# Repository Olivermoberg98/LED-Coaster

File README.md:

# LED Coaster

A battery-powered drink coaster with two rings of addressable RGB LEDs, controlled
from an Android phone over Bluetooth LE. The repository holds the whole project:
ESP32-C3 firmware, the Android app, the KiCad board and the 3D-printed enclosure.

- **Coaster:** 90 mm round board, ESP32-C3, 10 LEDs on the front and 20 around
  the back, a 1S Li-Po charged over USB-C, and a slide switch.
- **App:** finds coasters, sets each ring's pattern (fixed, pulse, chaser,
  rainbow) and colour, shows battery and charge state, and runs party games
  across several coasters at once.
- **Firmware:** reports battery voltage, percentage and charger state to the
  app, caps LED current as the cell runs down, and shuts off before the cell is
  empty.

## How it fits together

```
 Android app  ── BLE write:  Package 1 (rings on/off), Package 2 (pattern + colour) ──▶  coaster
              ◀── BLE notify: Package 3 (battery voltage, %, charger state) ──────────
```

The coaster is a GATT server with one command characteristic and one status
characteristic. Every packet carries a one-byte checksum, and the firmware drops
any packet that fails to parse. Byte layouts, UUIDs and the rules both sides
must keep in step are in [CLAUDE.md](CLAUDE.md#the-ble-contract-the-thing-that-spans-both-halves).

| Folder | Contents |
|---|---|
| [`Software/LED_coaster/`](Software/LED_coaster/) | Firmware: PlatformIO, Arduino, FastLED, NimBLE |
| [`Software/App/Coaster_app/`](Software/App/Coaster_app/) | Android app: Kotlin, Jetpack Compose, Nordic BLE library |
| [`Hardware/PCB/`](Hardware/PCB/) | KiCad project, JLCPCB production files, board checker; see its [README](Hardware/PCB/README.md) |
| [`Hardware/3d_printing/`](Hardware/3d_printing/) | Enclosure: STEP source plus print-ready STL/3MF for the top shell and bottom piece |

[CLAUDE.md](CLAUDE.md) and [the app's CLAUDE.md](Software/App/Coaster_app/CLAUDE.md)
are the detailed developer guides: architecture, protocol, power budget,
bring-up measurements and the battery discharge curve. They are written as
instructions for the Claude Code assistant but read fine as engineering notes.

## Building

### Firmware

Needs [PlatformIO](https://platformio.org/install/cli). Flashing and the serial
log both go over the coaster's USB-C port; no adapter is needed.

```sh
cd Software/LED_coaster
pio run                  # build
pio run -t upload        # flash
pio device monitor       # serial log
```

Every coaster needs its own ID. Set `coasterID` in
[`src/main.cpp`](Software/LED_coaster/src/main.cpp) before flashing each board.
It becomes the Bluetooth name `Coaster-<id>`. Two extra environments exist for
testing: `battery-fake` cycles through every battery and charger state for app
development, and `rundown` logs a full discharge to flash for fitting the
battery curve.

### Android app

Needs Android Studio, or the Android SDK with JDK 17. The app runs on
Android 12 (API 31) and newer, and needs a real phone, because the emulator has
no Bluetooth.

```sh
cd Software/App/Coaster_app
./gradlew assembleDebug  # build (gradlew.bat on Windows)
./gradlew installDebug   # install on a connected phone
./gradlew test lint      # unit tests and lint
```

### PCB

Open `Hardware/PCB/LED_Coaster.kicad_pro` in KiCad 10. The board was assembled
by JLCPCB from the files in `production/`, with the back side soldered by
hand. [`Hardware/PCB/README.md`](Hardware/PCB/README.md) covers the design
rules, part choices and assembly.

### Enclosure

The STL and 3MF files are already oriented for printing; the top shell prints
top face down. The coasters use black PLA, so use PETG if one must take hot
drinks. For the top shell's 0.5 mm LED slits, print at 0.12 mm layers and
keep X-Y hole compensation at 0, because the board is a deliberately snug fit.
Clear tape inside the top shell keeps condensation out of the slits.

## Using it

1. Switch the coaster on. It advertises as `Coaster-<id>`.
2. In the app, tap **New device**, pick the coaster, and it connects. Saved
   coasters reconnect from the dropdown.
3. Choose which rings are on, a pattern and a colour. The rings only light
   while the app is connected.
4. **Go to Games** to place several coasters on circles (long-press and drag),
   then start *Nattduellen* or *Random drink*.

Plug in USB-C to charge. The small LED on the front is on while charging, blinks
slowly when the battery is full, and blinks fast on a fault. A charge from empty
takes a little over 3 hours. Leaving it plugged in is fine: the charger stops
when the battery is full and only starts again once it has dropped to about 90%.

Charge a flat coaster soon. Even switched off, the charger chip draws a little
from the battery, so one left flat drains far enough within weeks for the
battery's own protection to cut it off, and it then reads 0 V. Plugging in USB
usually brings it back. Replace the battery if it is swollen or gets warm while
charging. For storage longer than a few weeks, leave it about half charged.

## Status

Five boards have been made, and the front side is verified on hardware: the
ESP32-C3, USB flashing and logging, BLE control from the app, the inner LED
ring, charging, and battery and charger reporting. A full discharge and a full
charge from empty have been logged to calibrate the percentage and check the
voltage reading. Still to do:

- Solder and verify the outer ring (`D1`–`D20`) and its capacitors.
- Test the full 30-LED load with the firmware's current cap on a part-empty
  cell, where a brown-out would show up.
- See the charger's low-battery and temperature-fault states on real hardware.

## Safety

- The battery connector has no reverse-polarity protection. Check the polarity
  of a new battery lead (pin 1 GND, pin 2 +) before plugging it in.
- Use a **protected** single-cell Li-Po. The firmware's low-voltage cut-off
  does not replace the cell's own protection.
- The charger IC gets hot to the touch while charging (up to about 0.8 W at a
  low cell). That is normal.

## License

[MIT](LICENSE)

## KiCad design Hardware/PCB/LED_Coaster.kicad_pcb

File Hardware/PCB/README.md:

# PCB

KiCad 10 project for the coaster board: a 90 mm round, two-layer board with an
ESP32-C3 module, a Li-Po charger with power path, and two rings of
WS2812-compatible LEDs, 10 on the front and 20 on the back.

| File | What it is |
|---|---|
| `LED_Coaster.kicad_pro` / `.kicad_sch` / `.kicad_pcb` | The project, schematic and board |
| `LED_Coaster.kicad_sym`, `Library.pretty/` | Project symbol and footprint libraries |
| `production/` | JLCPCB outputs from the Fabrication Toolkit plugin: gerber zip, BOM, placement, IPC netlist |
| `fabrication-toolkit-options.json` | The plugin's settings; `EXCLUDE DNP` must stay `true` |
| `tools/pcb_check.py` | Connectivity and stray-copper checker, see [below](#checking-the-board) |

## The board

| | |
|---|---|
| Outline | 90 mm circle, centre at (150, 80) mm in board coordinates |
| Layers | 2, with a `GND` pour on both |
| Front | ESP32-C3-WROOM-02 `U1`, USB-C `J3`, charger `U3`, LDO `U4`, LED-rail switch `Q1` and `SW1`, inner ring `D21`–`D30` with `C16`–`C19`, battery-sense divider, charge LED `D34` |
| Back | Outer ring `D1`–`D20` with decoupling `C8`–`C15`, battery connector `J1` |

**Power path.** USB-C 5 V feeds the MCP73871 charger `U3`, which powers the
system rail `+SYS` from USB or the cell and charges the cell at 500 mA.
`SW1` drives the gate of the P-FET `Q1`, which switches `+SYS` onto
`+LED_PWR` for the LEDs. The 3.3 V LDO `U4` takes its enable from
`+LED_PWR`, so switching `SW1` off powers down the ESP32 as well. Charging
still works with `SW1` off, because `U3` sits upstream of the switch.

**ESP32-C3 pins**

| GPIO | Net | Use |
|---|---|---|
| IO0 | `/small_ring` | Inner ring data, `D21` → `D30` |
| IO1 | `/large_ring` | Outer ring data, `D1` → `D20` |
| IO4 | `/BAT_SENSE` | Cell voltage through a 470k/470k divider and 100 nF |
| IO5, IO6, IO10 | `/STAT1`, `/STAT2`, `/PG` | Charger status, open-drain, read with internal pull-ups |
| IO7 | `D34` | Charge LED, through 1k to GND |
| IO18, IO19 | USB D−, D+ | Native USB: flashing and serial log over the USB-C port |
| IO20, IO21 | UART0 | `J4` header, not fitted |

**How `U3` is strapped.** USB-port mode (`SEL` low), 500 mA input limit
(`PROG2` high), 500 mA charge current (`R2` 2k), 50 mA termination (`R15`
20k), thermistor disabled (`R14` 10k to GND), and safety timer disabled
(`TE` high). The input limit (450 mA typical) is what governs, so the cell
charges at about 420 mA once the ESP32 has its share. With the timer off, both
status outputs low can only mean a temperature fault. The firmware decodes the states per datasheet Table 5-1;
the root [CLAUDE.md](../../CLAUDE.md) has the table.

## Rules for changing the design

- **`+SYS` and `+BATT` must never touch.** Shorting them defeats the power
  path: the board appears to work but charges wrongly.
- **Nothing may pull `STAT1`, `STAT2` or `PG` up to `+5V`.** They go straight
  to ESP32 pins rated 3.6 V. The board's original status LEDs did exactly
  that and were removed for this reason. `PG` is pseudo open-drain with a
  diode path to `IN`, so with USB unplugged the ESP32 pull-up back-feeds about
  58 µA into `+5V`. That is harmless.
- **The charger must be the `-2CC` variant** (`MCP73871-2CCI/ML`, LCSC
  `C5121473`), which regulates to 4.20 V and has LBO at 3.1 V. `C637761` is the
  `-4CA` variant: it charges to **4.40 V** and would overcharge a standard
  Li-Po.
- **Keep total system load near 1 A or below.** The charger's BAT→SYS path is
  about 200 mΩ. All 30 LEDs at full white draw about 1.08 A, enough to sag
  `+SYS` below the LDO's dropout on a part-discharged cell, so the firmware
  caps LED current.
- **Keep the thermal vias under `U3`, and keep the pour reaching them.** At
  about 420 mA into a low cell the charger dissipates up to about 0.8 W and
  gets hot.
- **Leave the netless zone on `B.Cu` at x 185–197, y 68–89.** It is the ESP32
  antenna keep-out.
- The battery-sense divider sits next to the ESP32, so the long trace is the
  low-impedance `+BATT` rather than the 235 kΩ divider node.
- `C20` is 22 µF. A bigger bulk capacitor does not help: droop on an LED step
  is set by the cell's resistance plus about 400 mΩ in the path, not by
  capacitance.

## Manufacturing

The first batch (September 2026) was 5 boards from JLCPCB with **Economic PCBA
on the front side only**: 20 BOM lines, 47 parts, about US$98 including
shipping. The back side is hand-soldered.

**LED part.** The LEDs are TUOZHAN **TZ-5050S2RGB-5V-I4-H1** (`C26167850`), a
WS2812B-compatible part. The BOM still calls them WS2812B. Every real WS2812B is
MSL 5a and rated for 240 °C peak, and JLCPCB refuses them for Economic
assembly, which reflows at 255 °C. Its part pages may list them as Economic, but
only the cart decides. The TZ part is MSL 3 and rated for 250 °C. It has the same
1 = VDD, 2 = DOUT, 3 = GND, 4 = DIN pinout, so it fits the footprint at 0°.

> **Do not substitute an SK6812 without a 180° rotation offset.** Its pinout
> is 1 = GND, 2 = DIN, 3 = VDD, 4 = DOUT. At 0° the supply is reversed and
> every LED on the board is destroyed at power-up.

**DNP.** The only thing that keeps a part out of the BOM is `(dnp yes)` on the
schematic symbol. A part without an `MPN` is not dropped; it appears as a line
with an empty LCSC number, which JLCPCB cannot source. The back-side parts,
`J1`, `J4`, `Btn1`–`Btn4` and the mounting holes are DNP. Set DNP in the
schematic, because *Update PCB from Schematic* overwrites a board-only change.

**Regenerating `production/`.** Run the Fabrication Toolkit plugin from the
board editor. Then check `bom.csv`: it should have 20 lines and 47 parts, the
LED line should have a quantity of **10** (30 means the DNP flags were lost),
and `U1` should appear once. In JLCPCB's placement preview, check one LED per
ring. All 30 share one orientation, so if one is right they all are. If one is
wrong, correct it with an `FT Rotation Offset` field on the symbols rather than
editing the placement file.

**DRC constraints** used for JLCPCB's standard process: track and clearance
0.15 mm, via 0.6 mm / 0.3 mm drill, annular ring 0.13 mm, hole-to-hole 0.5 mm,
**copper to edge 0.30 mm**, and **minimum through hole 0.20 mm**. KiCad's
default copper-to-edge of 0.0 mm never fires, and 0.30 mm minimum through hole
flags the 0.20 mm and 0.25 mm thermal vias inside the `U3` and `U1` footprints.

**Current DRC and ERC status.** DRC has 0 errors, 0 unconnected items and 0
schematic-parity issues. It reports 95 warnings, all cosmetic or library-related:
62 silkscreen over copper, 14 silkscreen overlaps, 2 silkscreen at the board
edge, 16 footprints that differ from the KiCad 10 library copies, and 1
missing library. ERC has 0 errors and 39 warnings, 35 of them off-grid wire
ends in the LED-ring wiring. The missing library is the ESP32-C3-WROOM-02's.
Its symbol and footprint are embedded in the schematic and board, so the design
is complete, but they are not in the project libraries yet.

## Hand-soldering

| Stage | Parts | What it adds |
|---|---|---|
| 1 | `J1` | Battery, so charging, BLE and the inner ring work |
| 2 | `D1`–`D20`, `C8`–`C15` (100 nF 0603) | The outer ring |

- `J1` is a JST-EH 2.5 mm connector: **pin 1 GND, pin 2 `+BATT`**. There is no
  reverse-polarity protection, so check a new battery lead with a meter first,
  and use a protected cell.
- TZ-5050S2RGB limits from its datasheet: iron at **≤ 315 °C, under 3 s per
  joint, once only**, and the tip must not touch the lens. To make that
  possible, the outer-ring LED and capacitor pads connect to the `GND` pour
  through thermal relief. Everywhere else the pour connects solid, for reflow.
- The outer ring is one data chain, `D1` → `D20`, fed from IO1 into `D1`
  pin 4. A dead or badly soldered LED leaves everything after it dark. If the
  ring lights up to `Dn`, look at `Dn`'s DOUT and `Dn+1`.
- The footprint is a hand-solder variant with extended, slightly asymmetric
  pads. Machine-placed LEDs sit about 0.14 mm off-centre, which is expected.
- `Btn1`–`Btn4` are not fitted. The firmware reads none of them, and `Btn3`
  (boot) and `Btn4` (enable) are not needed for flashing over native USB. A
  replacement must match the land pattern: two 1.80 × 1.10 mm pads plus two
  mechanical pads in an 8.6 × 9.3 mm envelope.

## Checking the board

`tools/pcb_check.py` reads the `.kicad_pcb` directly. It needs only the Python
standard library, no KiCad install. It answers what DRC does not: whether each
net is really one connected island, which pad is stranded, and whether stray
copper is left over. CI runs `all` on every push and fails on any problem.

```sh
cd Hardware/PCB/tools
python pcb_check.py all            # nets + zones + shorts + strays
python pcb_check.py net "+LED_PWR" # one net: groups and every copper item
python pcb_check.py rings          # LED chain continuity and ring uniformity
python pcb_check.py --help         # every subcommand
```

Refill the zones (<kbd>B</kbd>) and save before trusting any result, because
the checker reads the stored fill. The header of the script lists the parsing
traps it handles. The main one is that back-side pads are **not** mirrored in X.

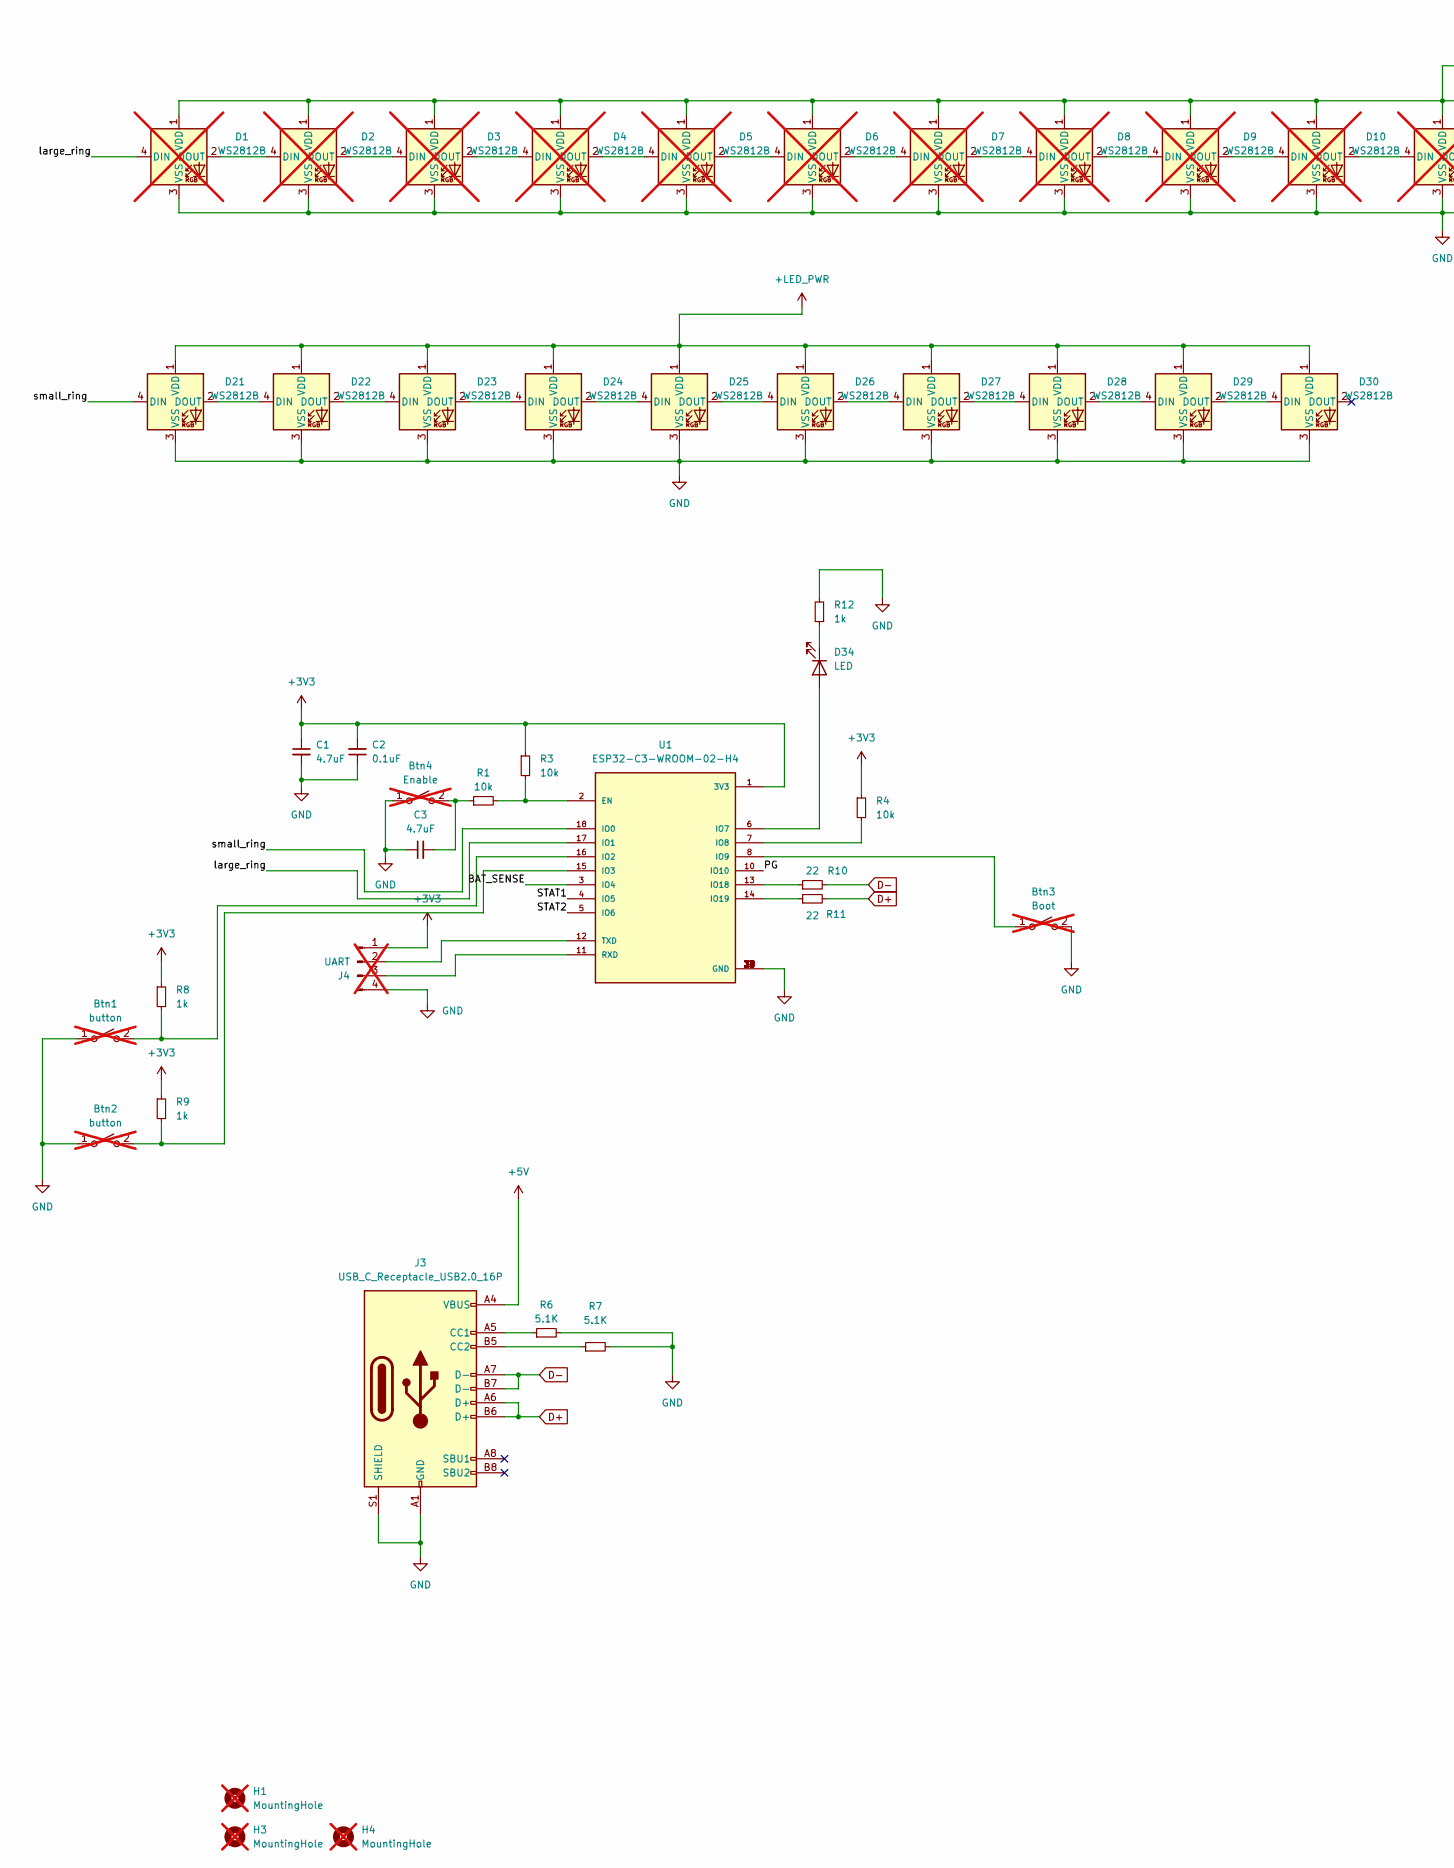
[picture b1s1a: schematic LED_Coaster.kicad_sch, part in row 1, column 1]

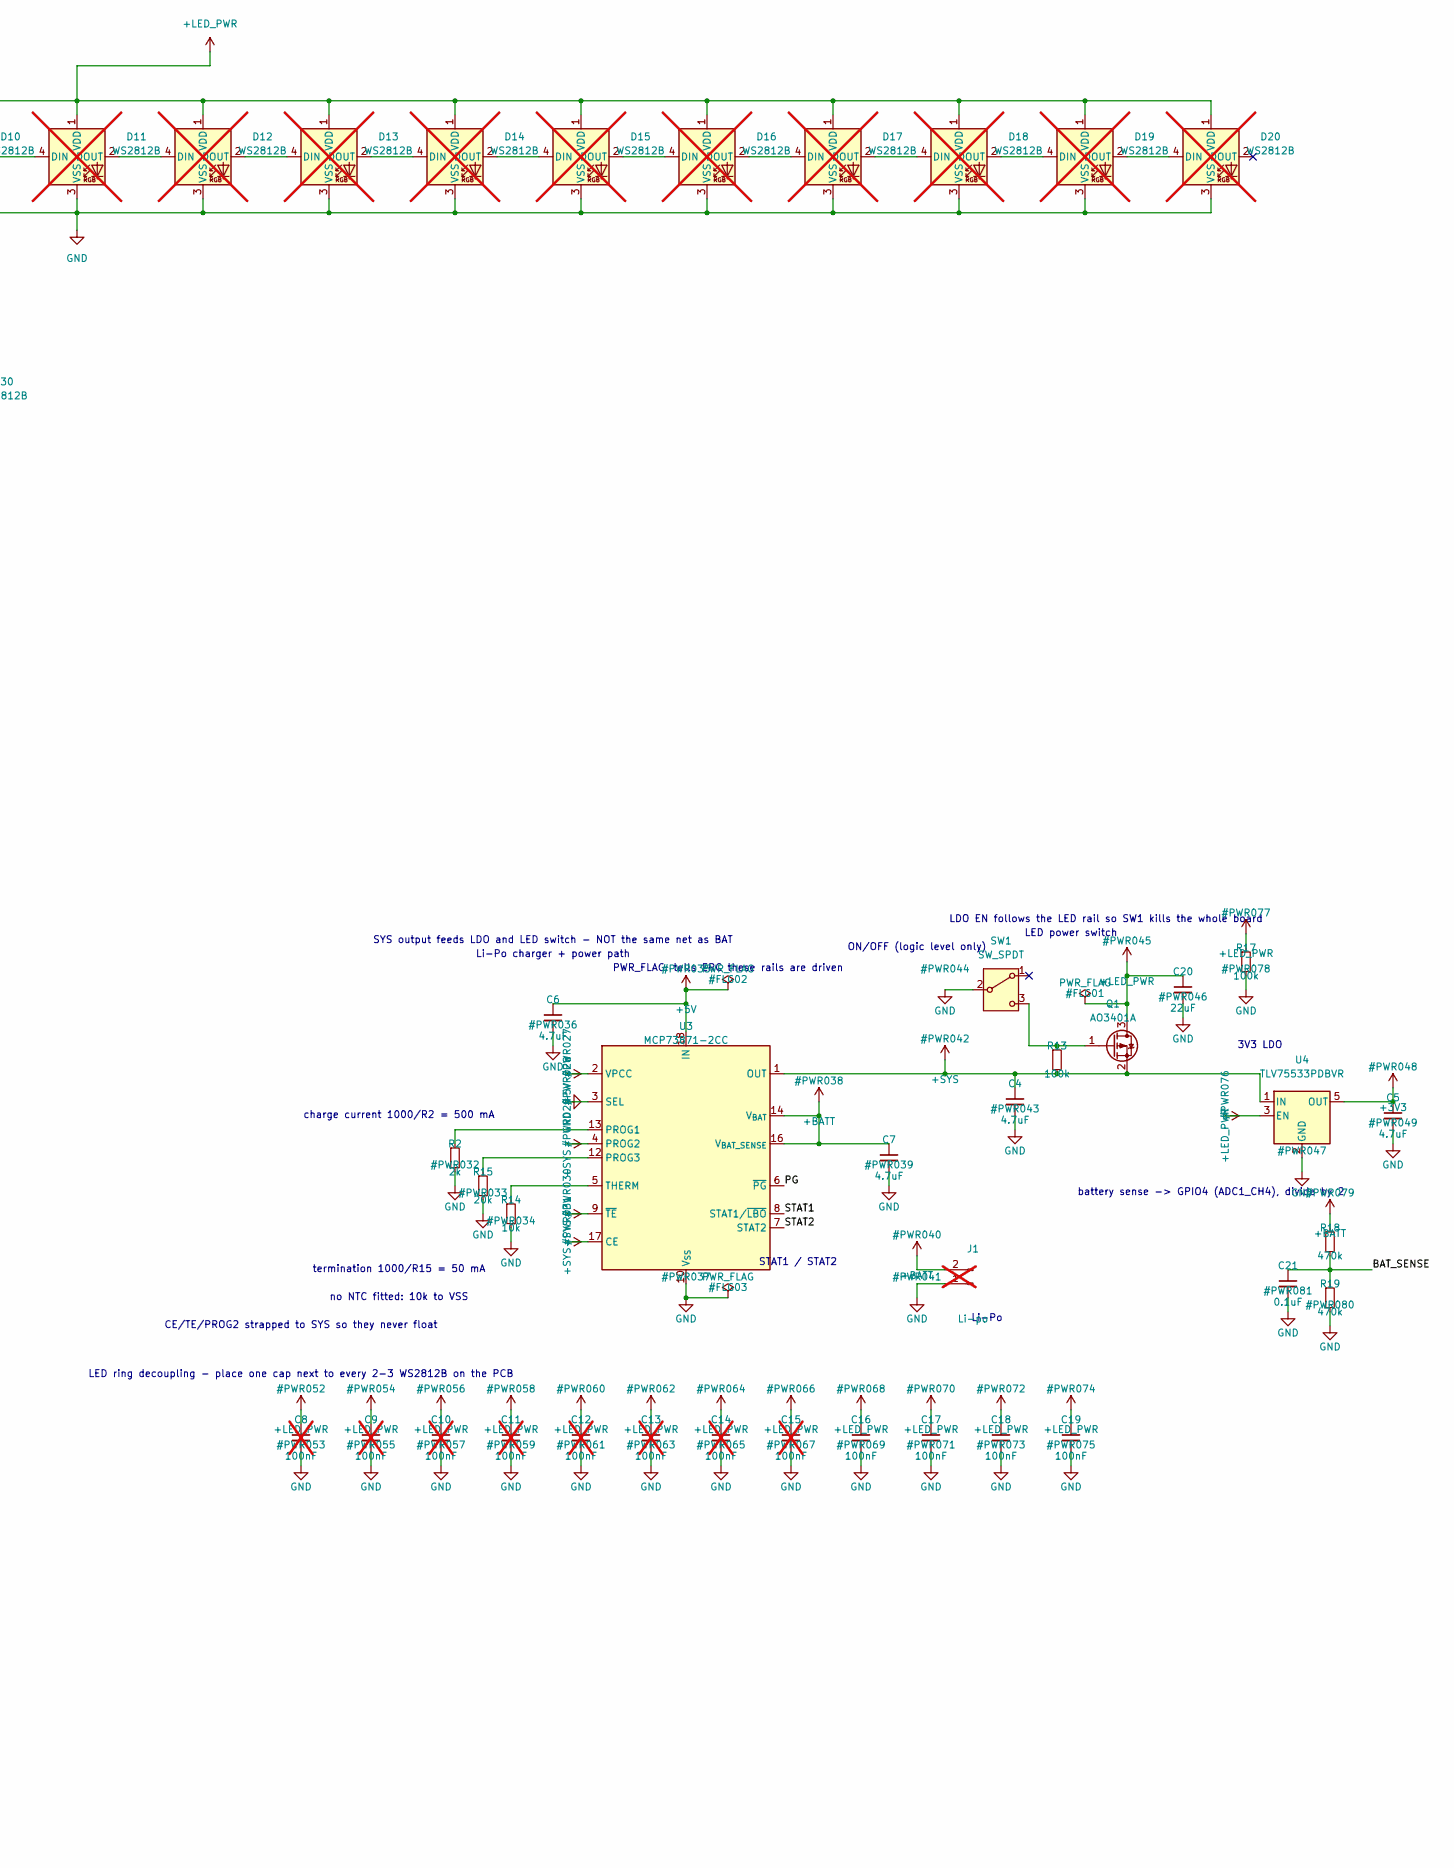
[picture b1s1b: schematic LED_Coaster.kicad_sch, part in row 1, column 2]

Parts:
Btn1, Btn2: button; SW_SPST_SKQG_WithStem; MPN C318884; not fitted
Btn3: Boot; SW_SPST_SKQG_WithStem; MPN C318884; not fitted
Btn4: Enable; SW_SPST_SKQG_WithStem; MPN C318884; not fitted
C1, C3, C4, C5, C6, C7: 4.7uF; C_0805_2012Metric_Pad1.18x1.45mm_HandSolder; MPN C1779
C2, C21: 0.1uF; C_0805_2012Metric_Pad1.18x1.45mm_HandSolder; MPN C28233
C8, C9, C10, C11, C12, C13, C14, C15: 100nF; C_0603_1608Metric_Pad1.08x0.95mm_HandSolder; MPN C14663; not fitted
C16, C17, C18, C19: 100nF; C_0603_1608Metric_Pad1.08x0.95mm_HandSolder; MPN C14663
C20: 22uF; C_0805_2012Metric_Pad1.18x1.45mm_HandSolder; MPN C380336
D1, D2, D3, D4, D5, D6, D7, D8, D9, D10, D11, D12, D13, D14, D15, D16, D17, D18, D19, D20: WS2812B; LED_WS2812_5050_handsolder; MPN C26167850; not fitted
D21, D22, D23, D24, D25, D26, D27, D28, D29, D30: WS2812B; LED_WS2812_5050_handsolder; MPN C26167850
D34: LED; LED_0805_2012Metric_Pad1.15x1.40mm_HandSolder; MPN C2297
H1, H3, H4: MountingHole; MountingHole_4.3mm_M4_Pad_Via; not fitted
J1: Li-po; JST_EH_S2B-EH_1x02_P2.50mm_Horizontal; not fitted
J3: USB_C_Receptacle_USB2.0_16P; USB_C_Receptacle_HRO_TYPE-C-31-M-12; MPN C165948
J4: UART; PinHeader_1x04_P2.54mm_Vertical; not fitted
Q1: AO3401A; SOT-23; MPN C15127
R1, R3, R4, R14: 10k; R_0805_2012Metric_Pad1.20x1.40mm_HandSolder; MPN C17414
R2: 2k; R_0805_2012Metric_Pad1.20x1.40mm_HandSolder; MPN C17604
R6, R7: 5.1K; R_0805_2012Metric_Pad1.20x1.40mm_HandSolder; MPN C27834
R8, R9, R12: 1k; R_0805_2012Metric_Pad1.20x1.40mm_HandSolder; MPN C17513
R10, R11: 22; R_0805_2012Metric_Pad1.20x1.40mm_HandSolder; MPN C17561
R13, R17: 100k; R_0805_2012Metric_Pad1.20x1.40mm_HandSolder; MPN C149504
R15: 20k; R_0805_2012Metric_Pad1.20x1.40mm_HandSolder; MPN C4328
R18, R19: 470k; R_0805_2012Metric_Pad1.20x1.40mm_HandSolder; MPN C17709
SW1: SW_SPDT; SW_SPDT_CK_JS102011SAQN; MPN C221660
U1: ESP32-C3-WROOM-02-H4; MODULE_ESP32-C3-WROOM-02-H4; MPN C2944070
U3: MCP73871-2CC; QFN-20-1EP_4x4mm_P0.5mm_EP2.5x2.5mm_ThermalVias; MPN C5121473
U4: TLV75533PDBVR; SOT-23-5; MPN C404027

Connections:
+3V3: C1.1, C2.2, C5.1, J4.1, R3.1, R4.1, R8.1, R9.1, U1.1 (3V3), U4.5 (OUT)
+5V: C6.1, J3.A4 (VBUS), J3.A9 (VBUS), J3.B4 (VBUS), J3.B9 (VBUS), U3.2 (VPCC), U3.18 (IN), U3.19 (IN)
+BATT: C7.1, J1.2, R18.1, U3.14 (V_{BAT}), U3.15 (V_{BAT}), U3.16 (V_{BAT_SENSE})
+LED_PWR: C8.1, C9.1, C10.1, C11.1, C12.1, C13.1, C14.1, C15.1, C16.1, C17.1, C18.1, C19.1, C20.1, D1.1 (VDD), D2.1 (VDD), D3.1 (VDD), D4.1 (VDD), D5.1 (VDD), D6.1 (VDD), D7.1 (VDD), D8.1 (VDD), D9.1 (VDD), D10.1 (VDD), D11.1 (VDD), D12.1 (VDD), D13.1 (VDD), D14.1 (VDD), D15.1 (VDD), D16.1 (VDD), D17.1 (VDD), D18.1 (VDD), D19.1 (VDD), D20.1 (VDD), D21.1 (VDD), D22.1 (VDD), D23.1 (VDD), D24.1 (VDD), D25.1 (VDD), D26.1 (VDD), D27.1 (VDD), D28.1 (VDD), D29.1 (VDD), D30.1 (VDD), Q1.3 (D), R17.1, U4.3 (EN)
+SYS: C4.1, Q1.2 (S), R13.2, U3.1 (OUT), U3.4 (PROG2), U3.9 (~TE), U3.17 (CE), U3.20 (OUT), U4.1 (IN)
/BAT_SENSE: C21.1, R18.2, R19.1, U1.3 (IO4)
/PG: U1.10 (IO10), U3.6 (~PG)
/STAT1: U1.4 (IO5), U3.8 (STAT1/~LBO)
/STAT2: U1.5 (IO6), U3.7 (STAT2)
/large_ring: D1.4 (DIN), U1.17 (IO1)
/small_ring: D21.4 (DIN), U1.18 (IO0)
D+: J3.A6 (D+), J3.B6 (D+), R11.2
D-: J3.A7 (D-), J3.B7 (D-), R10.2
GND: Btn1.1 (A), Btn2.1 (A), Btn3.2 (B), Btn4.1 (A), C1.2, C2.1, C3.1, C4.2, C5.2, C6.2, C7.2, C8.2, C9.2, C10.2, C11.2, C12.2, C13.2, C14.2, C15.2, C16.2, C17.2, C18.2, C19.2, C20.2, C21.2, D1.3 (VSS), D2.3 (VSS), D3.3 (VSS), D4.3 (VSS), D5.3 (VSS), D6.3 (VSS), D7.3 (VSS), D8.3 (VSS), D9.3 (VSS), D10.3 (VSS), D11.3 (VSS), D12.3 (VSS), D13.3 (VSS), D14.3 (VSS), D15.3 (VSS), D16.3 (VSS), D17.3 (VSS), D18.3 (VSS), D19.3 (VSS), D20.3 (VSS), D21.3 (VSS), D22.3 (VSS), D23.3 (VSS), D24.3 (VSS), D25.3 (VSS), D26.3 (VSS), D27.3 (VSS), D28.3 (VSS), D29.3 (VSS), D30.3 (VSS), J1.1, J3.A1 (GND), J3.A12 (GND), J3.B1 (GND), J3.B12 (GND), J3.S1 (SHIELD), J4.4, R2.2, R6.2, R7.2, R12.2, R14.2, R15.2, R17.2, R19.2, SW1.2 (B), U1.9 (GND), U1.19 (GND), U1.20 (GND), U1.21 (GND), U1.22 (GND), U1.23 (GND), U1.24 (GND), U1.25 (GND), U1.26 (GND), U1.27 (GND), U1.28 (GND), U1.29 (GND), U1.30 (GND), U1.31 (GND), U1.32 (GND), U1.33 (GND), U1.34 (GND), U1.35 (GND), U1.36 (GND), U1.37 (GND), U1.38 (GND), U1.39 (GND), U3.3 (SEL), U3.10 (V_{SS}), U3.11 (V_{SS}), U3.21 (V_{SS}), U4.2 (GND)
unnamed: Btn1.2 (B), R8.2, U1.16 (IO2)
unnamed: Btn2.2 (B), R9.2, U1.15 (IO3)
unnamed: Btn3.1 (A), U1.8 (IO9)
unnamed: Btn4.2 (B), C3.2, R1.1
unnamed: D1.2 (DOUT), D2.4 (DIN)
unnamed: D2.2 (DOUT), D3.4 (DIN)
unnamed: D3.2 (DOUT), D4.4 (DIN)
unnamed: D4.2 (DOUT), D5.4 (DIN)
unnamed: D5.2 (DOUT), D6.4 (DIN)
unnamed: D6.2 (DOUT), D7.4 (DIN)
unnamed: D7.2 (DOUT), D8.4 (DIN)
unnamed: D8.2 (DOUT), D9.4 (DIN)
unnamed: D9.2 (DOUT), D10.4 (DIN)
unnamed: D10.2 (DOUT), D11.4 (DIN)
unnamed: D11.2 (DOUT), D12.4 (DIN)
unnamed: D12.2 (DOUT), D13.4 (DIN)
unnamed: D13.2 (DOUT), D14.4 (DIN)
unnamed: D14.2 (DOUT), D15.4 (DIN)
unnamed: D15.2 (DOUT), D16.4 (DIN)
unnamed: D16.2 (DOUT), D17.4 (DIN)
unnamed: D17.2 (DOUT), D18.4 (DIN)
unnamed: D18.2 (DOUT), D19.4 (DIN)
unnamed: D19.2 (DOUT), D20.4 (DIN)
unnamed: D21.2 (DOUT), D22.4 (DIN)
unnamed: D22.2 (DOUT), D23.4 (DIN)
unnamed: D23.2 (DOUT), D24.4 (DIN)
unnamed: D24.2 (DOUT), D25.4 (DIN)
unnamed: D25.2 (DOUT), D26.4 (DIN)
unnamed: D26.2 (DOUT), D27.4 (DIN)
unnamed: D27.2 (DOUT), D28.4 (DIN)
unnamed: D28.2 (DOUT), D29.4 (DIN)
unnamed: D29.2 (DOUT), D30.4 (DIN)
unnamed: D34.2 (A), U1.6 (IO7)
unnamed: D34.1 (K), R12.1
unnamed: J3.A5 (CC1), R6.1
unnamed: J3.B5 (CC2), R7.1
unnamed: J4.2, U1.12 (TXD)
unnamed: J4.3, U1.11 (RXD)
unnamed: Q1.1 (G), R13.1, SW1.3 (C)
unnamed: R1.2, R3.2, U1.2 (EN)
unnamed: R4.2, U1.7 (IO8)
unnamed: R10.1, U1.13 (IO18)
unnamed: R11.1, U1.14 (IO19)
unnamed: R2.1, U3.13 (PROG1)
unnamed: R15.1, U3.12 (PROG3)
unnamed: R14.1, U3.5 (THERM)

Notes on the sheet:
Li-Po charger + power path
SYS output feeds LDO and LED switch - NOT the same net as BAT
charge current 1000/R2 = 500 mA
termination 1000/R15 = 50 mA
no NTC fitted: 10k to VSS
CE/TE/PROG2 strapped to SYS so they never float
ON/OFF (logic level only)
LED power switch
3V3 LDO
Li-Po
STAT1 / STAT2
LED ring decoupling - place one cap next to every 2-3 WS2812B on the PCB
LDO EN follows the LED rail so SW1 kills the whole board
battery sense -> GPIO4 (ADC1_CH4), divide by 2
PWR_FLAG: tells ERC these rails are driven

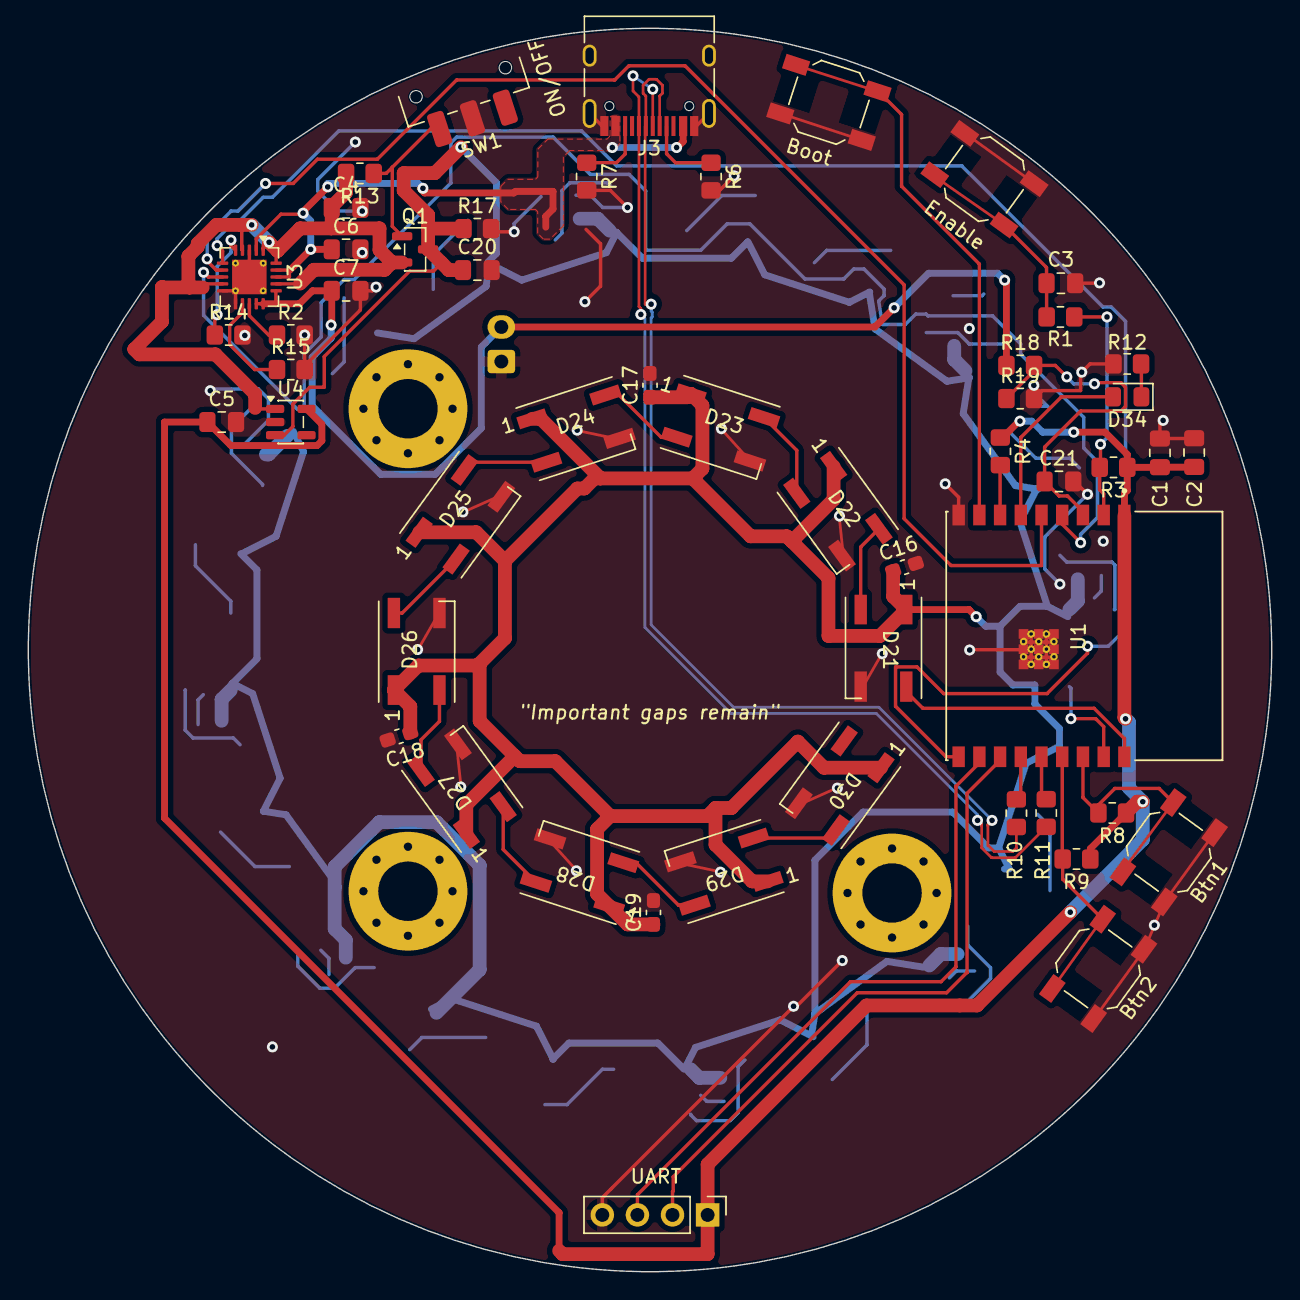
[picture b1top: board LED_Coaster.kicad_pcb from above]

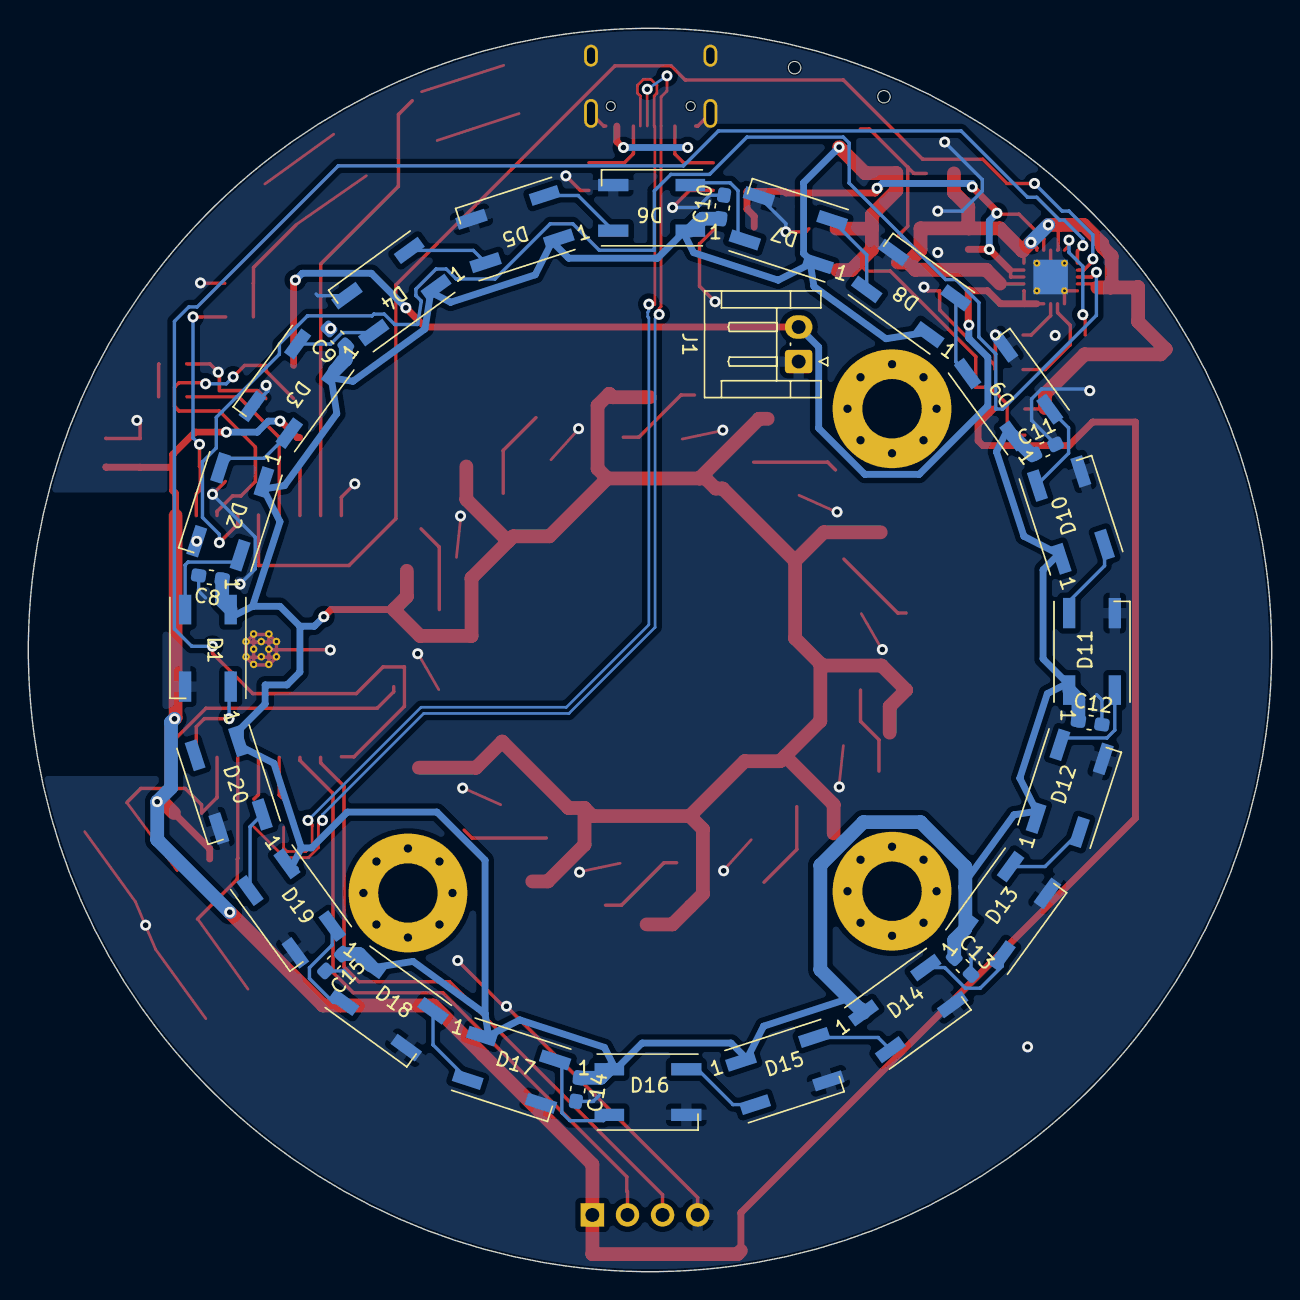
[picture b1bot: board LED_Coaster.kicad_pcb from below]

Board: 2 copper layers, 90.0 x 90.0 mm, 84 parts (29 on the bottom side), 60 nets.

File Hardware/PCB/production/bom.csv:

Designator,Footprint,Quantity,Value,LCSC Part #
"C1, C3, C4, C5, C6, C7",0805,6,4.7uF,C1779
"C16, C17, C18, C19",0603,4,100nF,C14663
"C2, C21",0805,2,0.1uF,C28233
C20,0805,1,22uF,C380336
"D21, D22, D23, D24, D25, D26, D27, D28, D29, D30",LED_WS2812_5050_handsolder,10,WS2812B,C26167850
D34,0805,1,LED,C2297
J3,USB_C_Receptacle_HRO_TYPE-C-31-M-12,1,USB_C_Receptacle_USB2.0_16P,C165948
Q1,SOT-23,1,AO3401A,C15127
"R1, R14, R3, R4",0805,4,10k,C17414
"R10, R11",0805,2,22,C17561
"R12, R8, R9",0805,3,1k,C17513
"R13, R17",0805,2,100k,C149504
R15,0805,1,20k,C4328
"R18, R19",0805,2,470k,C17709
R2,0805,1,2k,C17604
"R6, R7",0805,2,5.1K,C27834
SW1,SW_SPDT_CK_JS102011SAQN,1,SW_SPDT,C221660
U1,MODULE_ESP32-C3-WROOM-02-H4,1,ESP32-C3-WROOM-02-H4,C2944070
U3,QFN-20-1EP_4x4mm_P0.5mm_EP2.5x2.5mm_ThermalVias,1,MCP73871-2CC,C5121473
U4,SOT-23-5,1,TLV75533PDBVR,C404027

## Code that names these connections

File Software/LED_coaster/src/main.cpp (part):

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BLEHandler blehandler(coasterID);

// Battery sense: +BATT through a 470k/470k divider, so the pin sees half the cell.
const int BAT_SENSE_PIN = 4;
// MCP73871 status outputs, all open-drain (High-Z reads HIGH with the pull-ups).
const int STAT1_PIN = 5;
const int STAT2_PIN = 6;
const int PG_PIN = 10;
// D34, through R12 (1k) to GND: the board's only charge indicator.
const int CHARGE_LED_PIN = 7;
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  const int samples = 16;
  uint32_t sum = 0;
  for (int i = 0; i < samples; i++) {
    sum += analogReadMilliVolts(BAT_SENSE_PIN);
  }
  return (sum / samples) * 2;
}
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// Decodes the status outputs per MCP73871 datasheet Table 5-1.
ChargerState chargerState() {
  bool pg = digitalRead(PG_PIN);
  bool stat1 = digitalRead(STAT1_PIN);
  bool stat2 = digitalRead(STAT2_PIN);
  if (!pg && !stat1 && stat2)  return CHARGER_CHARGING;
  if (!pg && stat1 && !stat2)  return CHARGER_COMPLETE;
  if (!pg && !stat1 && !stat2) return CHARGER_TEMP_FAULT;
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// Reads the battery and charger, logs them, and loads Package 3 into the status
// characteristics. Returns true when the reported charger state changed.
bool updateBatteryStatus() {
  uint8_t pins = digitalRead(PG_PIN) | (digitalRead(STAT1_PIN) << 1) | (digitalRead(STAT2_PIN) << 2);
#ifdef BATTERY_STATUS_FAKE
  // Steps through every charger state and a falling voltage, one step per 5 s.
  uint32_t step = millis() / 5000;
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
  Serial.begin(9600);

  analogSetPinAttenuation(BAT_SENSE_PIN, ADC_11db);
  pinMode(STAT1_PIN, INPUT_PULLUP);
  pinMode(STAT2_PIN, INPUT_PULLUP);
  pinMode(PG_PIN, INPUT_PULLUP);
  pinMode(CHARGE_LED_PIN, OUTPUT);
  digitalWrite(CHARGE_LED_PIN, LOW);
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
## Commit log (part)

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2024-05-03 Added KiCad files
2024-05-03 Code for controlling the LED
2024-05-03 Added outer ring of LEDs
2024-05-03 Added inner ring of LEDs
2024-05-03 MCU schematic halfway done
2024-05-04 Placed all components
2024-05-04 Added traces and datasheets
2024-05-04 Added a fuse
2024-05-04 Version 1 done
2024-05-07 ny kod för coaster
2024-05-23 gjorde inget
2024-06-03 updated Kicad files
2024-11-05 Version 3 using esp32-C3
2024-11-12 New file structure
2024-11-13 ignore extensions.json
2024-11-13 Updates regarding Bluetooth and pattern selection
2024-11-13 App for connecting to the coaster and sending data via Bluetooth
2024-11-16 Added logic to handle data packages sent from the app
2024-11-17 Updated the data package functions to match the data from the app
2024-11-19 Added chaser pattern
2024-11-19 Exported step file of LED coaster V3
2024-11-19 Exported step file of LED coaster V3 (With components)
2024-11-20 Changing the pattern names in the app
2024-11-27 changed parameters
2024-12-01 update: Can rotate the phone and pick color for fixed state.
2024-12-08 Connect to the app via BLE GATT characteristics and change the color and mode of the LEDs
2024-12-09 Added a rainbow pattern
2024-12-11 Update of the rainbow function and some small fixes
2024-12-22 update to app: New game faeture
2024-12-22 update to app: Visually adjust the number of coasters you can play with
2024-12-23 update to app: Adding more try/catch to catch bugs
2024-12-26 update to app: Functions and UI for two new games to play with the coasters
2025-09-09 Correct bluetooth service
2026-01-04 some random .idea stuff
2026-01-04 new on and off feature
2026-01-06 update to app: Nattduellen is no working
2026-01-06 update to app: Better way of handling the selection of coaster to the games
2026-01-06 update to app: some small refactoring
2026-01-19 New state machine for the coaster
2026-01-22 Make sure fixed mode consumes less power
2026-01-22 Battery saving when not connected
2026-01-24 update to app: Make sure all UI containers width are adjusted based on screen size
2026-01-24 update to app: Change the app icon
2026-01-25 update to app: Update drinking game to have accelerating changes
2026-01-25 Update chaser to be bright outside of the chasing and make sure the rotating freq is consistent
